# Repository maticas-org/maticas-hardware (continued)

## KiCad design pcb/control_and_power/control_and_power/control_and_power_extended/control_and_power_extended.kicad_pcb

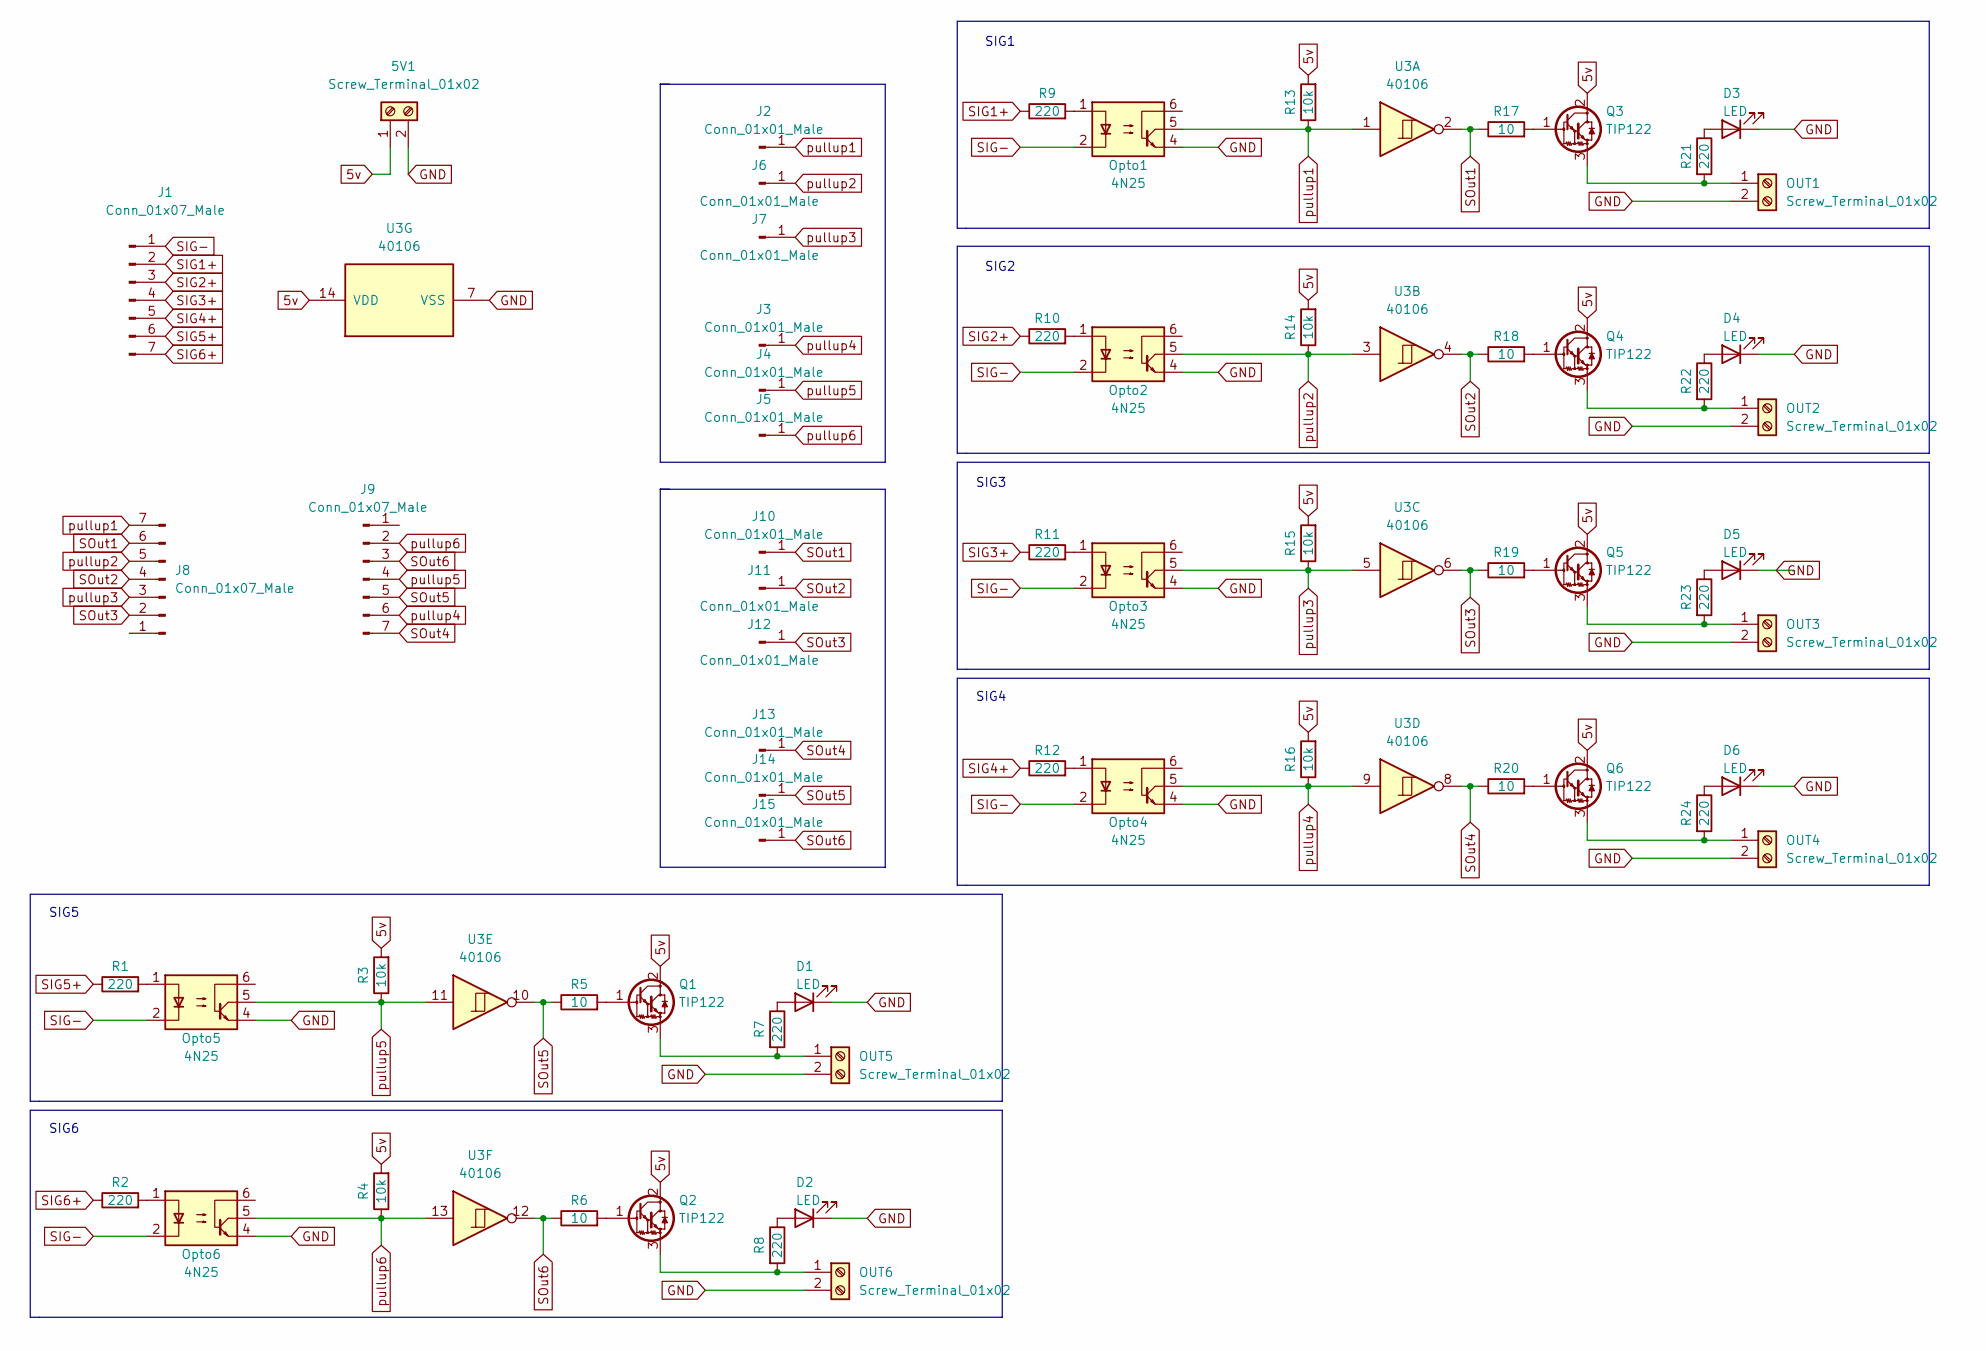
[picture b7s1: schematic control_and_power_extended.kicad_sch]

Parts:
5V1: Screw_Terminal_01x02; TerminalBlock_Altech_AK300-2_P5.00mm
D1, D2, D3, D4, D5, D6: LED; LED_D3.0mm_Clear
J1, J8, J9: Conn_01x07_Male; PinHeader_1x07_P2.54mm_Vertical
J2, J3, J4, J5, J6, J7, J10, J11, J12, J13, J14, J15: Conn_01x01_Male; PinHeader_1x01_P2.54mm_Vertical
OUT1, OUT2, OUT3, OUT4, OUT5, OUT6: Screw_Terminal_01x02; TerminalBlock_Altech_AK300-2_P5.00mm
Opto1, Opto2, Opto3, Opto4, Opto5, Opto6: 4N25; DIP-6_W7.62mm
Q1, Q2, Q3, Q4, Q5, Q6: TIP122; TO-220-3_Vertical
R1, R2, R7, R8, R9, R10, R11, R12, R21, R22, R23, R24: 220; R_Axial_DIN0204_L3.6mm_D1.6mm_P2.54mm_Vertical
R3, R4, R13, R14, R15, R16: 10k; R_Axial_DIN0204_L3.6mm_D1.6mm_P2.54mm_Vertical
R5, R6, R17, R18, R19, R20: 10; R_Axial_DIN0204_L3.6mm_D1.6mm_P2.54mm_Vertical
U3: 40106; DIP-14_W7.62mm

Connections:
5v: 5V1.1, Q1.2 (C), Q2.2 (C), Q3.2 (C), Q4.2 (C), Q5.2 (C), Q6.2 (C), R3.2, R4.2, R13.2, R14.2, R15.2, R16.2, U3.14 (VDD)
GND: 5V1.2, D1.1 (K), D2.1 (K), D3.1 (K), D4.1 (K), D5.1 (K), D6.1 (K), OUT1.2, OUT2.2, OUT3.2, OUT4.2, OUT5.2, OUT6.2, Opto1.4, Opto2.4, Opto3.4, Opto4.4, Opto5.4, Opto6.4, U3.7 (VSS)
unnamed: D1.2 (A), R7.1
unnamed: D2.2 (A), R8.1
unnamed: D3.2 (A), R21.1
unnamed: D4.2 (A), R22.1
unnamed: D5.2 (A), R23.1
unnamed: D6.2 (A), R24.1
unnamed: OUT1.1, Q3.3 (E), R21.2
unnamed: OUT2.1, Q4.3 (E), R22.2
unnamed: OUT3.1, Q5.3 (E), R23.2
unnamed: OUT4.1, Q6.3 (E), R24.2
unnamed: OUT5.1, Q1.3 (E), R7.2
unnamed: OUT6.1, Q2.3 (E), R8.2
unnamed: Q1.1 (B), R5.2
unnamed: Q2.1 (B), R6.2
unnamed: Q3.1 (B), R17.2
unnamed: Q4.1 (B), R18.2
unnamed: Q5.1 (B), R19.2
unnamed: Q6.1 (B), R20.2
unnamed: Opto5.1, R1.2
unnamed: Opto6.1, R2.2
unnamed: Opto1.1, R9.2
unnamed: Opto2.1, R10.2
unnamed: Opto3.1, R11.2
unnamed: Opto4.1, R12.2
SIG1+: J1.2, R9.1
SIG2+: J1.3, R10.1
SIG3+: J1.4, R11.1
SIG4+: J1.5, R12.1
SIG5+: J1.6, R1.1
SIG6+: J1.7, R2.1
SIG-: J1.1, Opto1.2, Opto2.2, Opto3.2, Opto4.2, Opto5.2, Opto6.2
SOut1: J8.6, J10.1, R17.1, U3.2
SOut2: J8.4, J11.1, R18.1, U3.4
SOut3: J8.2, J12.1, R19.1, U3.6
SOut4: J9.7, J13.1, R20.1, U3.8
SOut5: J9.5, J14.1, R5.1, U3.10
SOut6: J9.3, J15.1, R6.1, U3.12
pullup1: J2.1, J8.7, Opto1.5, R13.1, U3.1
pullup2: J6.1, J8.5, Opto2.5, R14.1, U3.3
pullup3: J7.1, J8.3, Opto3.5, R15.1, U3.5
pullup4: J3.1, J9.6, Opto4.5, R16.1, U3.9
pullup5: J4.1, J9.4, Opto5.5, R3.1, U3.11
pullup6: J5.1, J9.2, Opto6.5, R4.1, U3.13

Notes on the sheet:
SIG2
SIG3
SIG1
SIG4
SIG6
SIG5

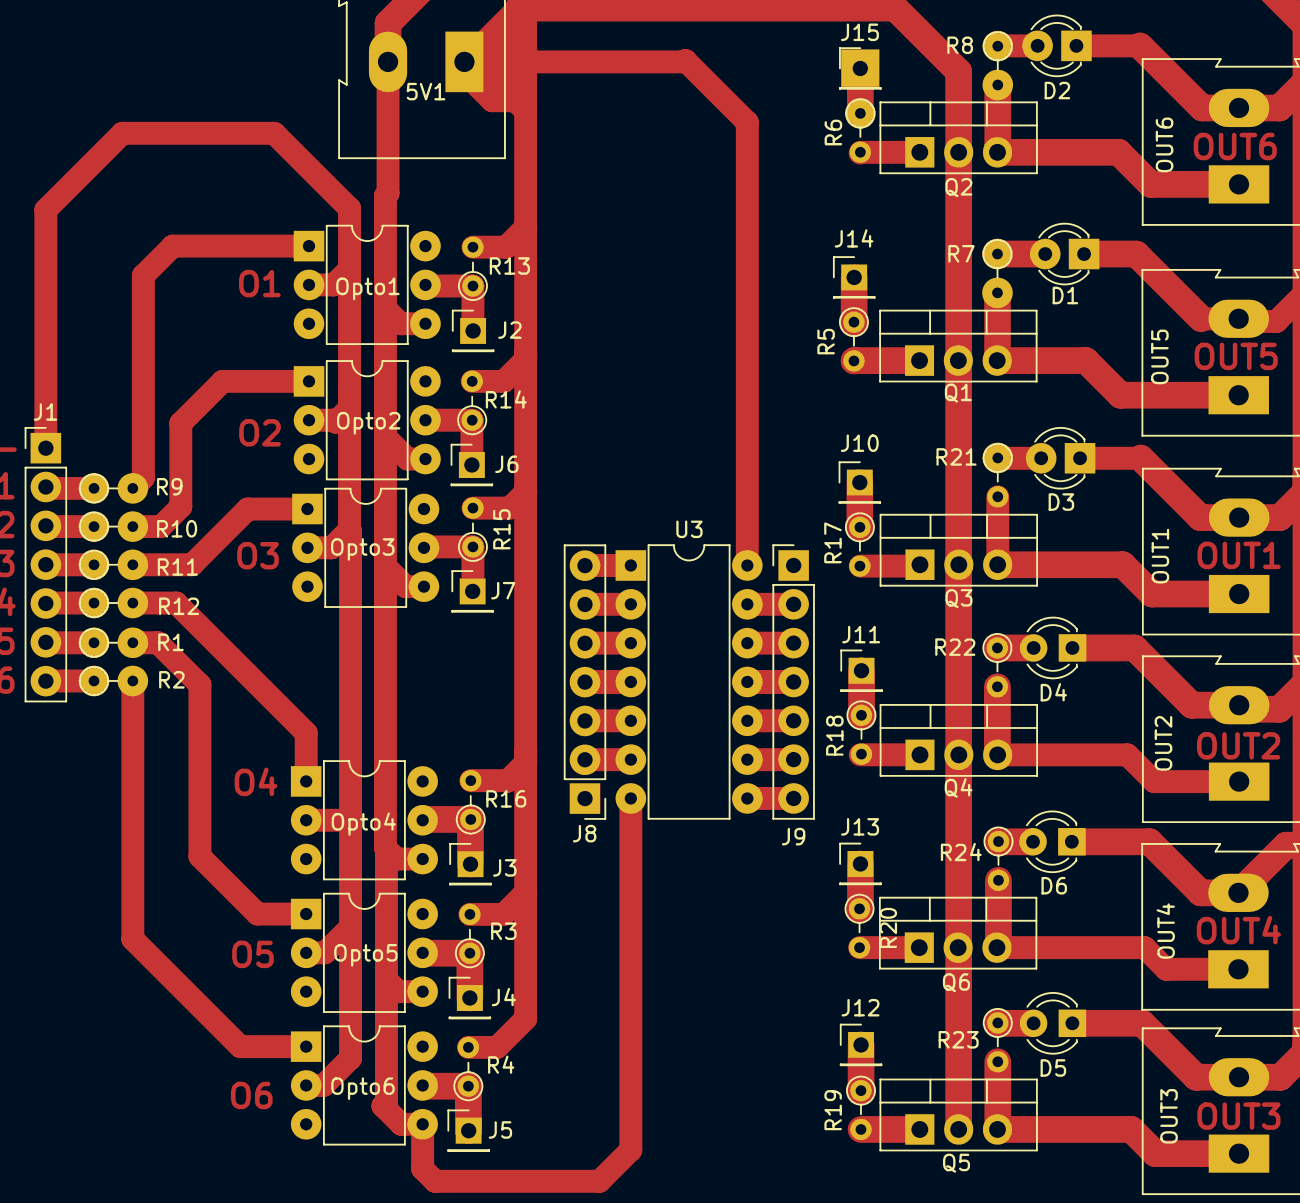
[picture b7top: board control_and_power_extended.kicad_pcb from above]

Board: 2 copper layers, 65 parts (0 on the bottom side), 45 nets.

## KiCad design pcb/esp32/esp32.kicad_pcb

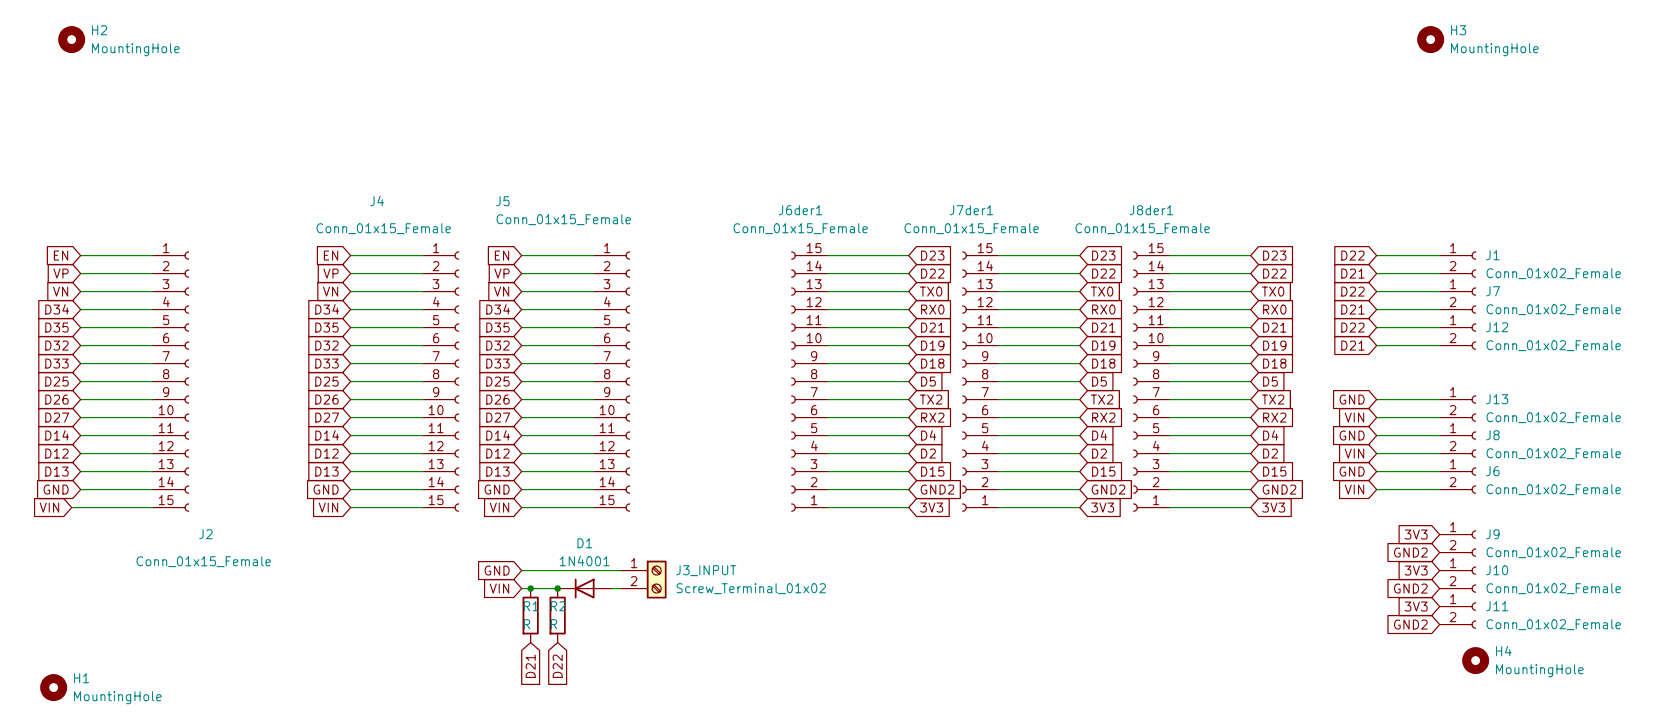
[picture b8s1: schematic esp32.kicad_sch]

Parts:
D1: 1N4001; D_DO-41_SOD81_P10.16mm_Horizontal
H1, H2, H3, H4: MountingHole; MountingHole_2.1mm
J1, J6, J7, J8, J9, J10, J11, J12, J13: Conn_01x02_Female; Connector_Molex_Molex_SL_171971-0004_1x02_P2.54mm_Vertical_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
J2, J4, J5, J6der1, J7der1, J8der1: Conn_01x15_Female; Connector_Molex_Molex_SL_171971-0015_1x15_P2.54mm_Vertical_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
J3_INPUT: Screw_Terminal_01x02; TerminalBlock_MetzConnect_Type055_RT01502HDWU_1x02_P5.00mm_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
R1: R; R_Axial_DIN0207_L6.3mm_D2.5mm_P15.24mm_Horizontal
R2: R; R_Axial_DIN0204_L3.6mm_D1.6mm_P7.62mm_Horizontal

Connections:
3V3: J6der1.1, J7der1.1, J8der1.1, J9.1, J10.1, J11.1
D2: J6der1.4, J7der1.4, J8der1.4
D4: J6der1.5, J7der1.5, J8der1.5
D5: J6der1.8, J7der1.8, J8der1.8
D12: J2.12, J4.12, J5.12
D13: J2.13, J4.13, J5.13
D14: J2.11, J4.11, J5.11
D15: J6der1.3, J7der1.3, J8der1.3
D18: J6der1.9, J7der1.9, J8der1.9
D19: J6der1.10, J7der1.10, J8der1.10
D21: J1.2, J6der1.11, J7.2, J7der1.11, J8der1.11, J12.2, R1.2
D22: J1.1, J6der1.14, J7.1, J7der1.14, J8der1.14, J12.1, R2.2
D23: J6der1.15, J7der1.15, J8der1.15
D25: J2.8, J4.8, J5.8
D26: J2.9, J4.9, J5.9
D27: J2.10, J4.10, J5.10
D32: J2.6, J4.6, J5.6
D33: J2.7, J4.7, J5.7
D34: J2.4, J4.4, J5.4
D35: J2.5, J4.5, J5.5
EN: J2.1, J4.1, J5.1
GND: J2.14, J3_INPUT.1, J4.14, J5.14, J6.1, J8.1, J13.1; also elsewhere on the board
GND2: J6der1.2, J7der1.2, J8der1.2, J9.2, J10.2, J11.2
unnamed 23: D1.2 (A), J3_INPUT.2; also elsewhere on the board
RX0: J6der1.12, J7der1.12, J8der1.12
RX2: J6der1.6, J7der1.6, J8der1.6
TX0: J6der1.13, J7der1.13, J8der1.13
TX2: J6der1.7, J7der1.7, J8der1.7
VIN: D1.1 (K), J2.15, J4.15, J5.15, J6.2, J8.2, J13.2, R1.1, R2.1
VN: J2.3, J4.3, J5.3
VP: J2.2, J4.2, J5.2

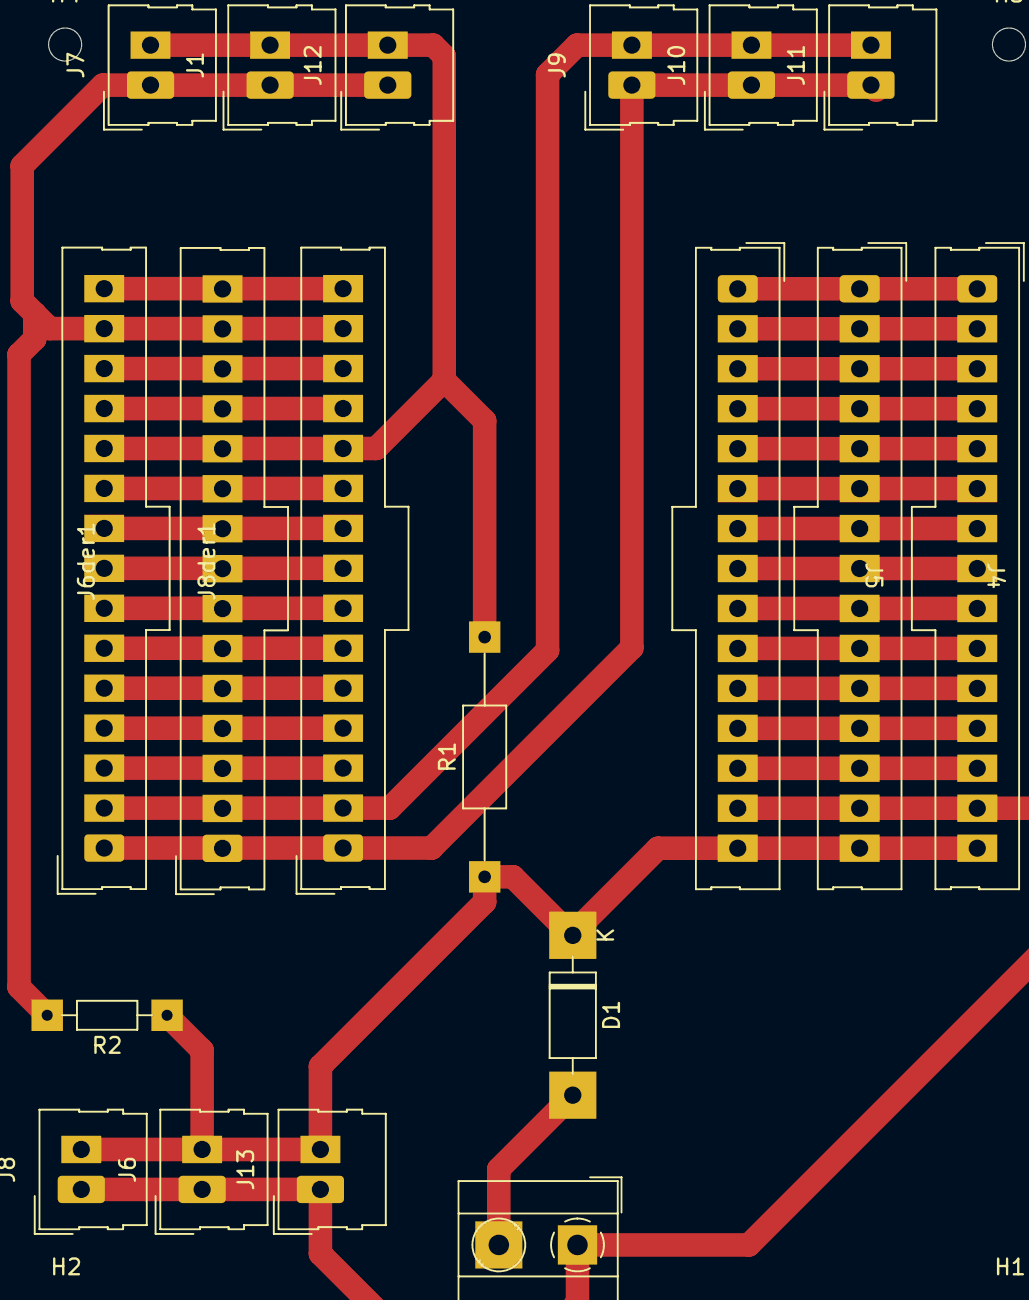
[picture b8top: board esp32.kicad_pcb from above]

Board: 2 copper layers, 23 parts (0 on the bottom side), 31 nets.

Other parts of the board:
J3: Screw_Terminal_01x02; TerminalBlock_MetzConnect_Type055_RT01502HDWU_1x02_P5.00mm_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

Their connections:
GND: J3.1; also elsewhere on the board
unnamed 23: J3.2; also elsewhere on the board
